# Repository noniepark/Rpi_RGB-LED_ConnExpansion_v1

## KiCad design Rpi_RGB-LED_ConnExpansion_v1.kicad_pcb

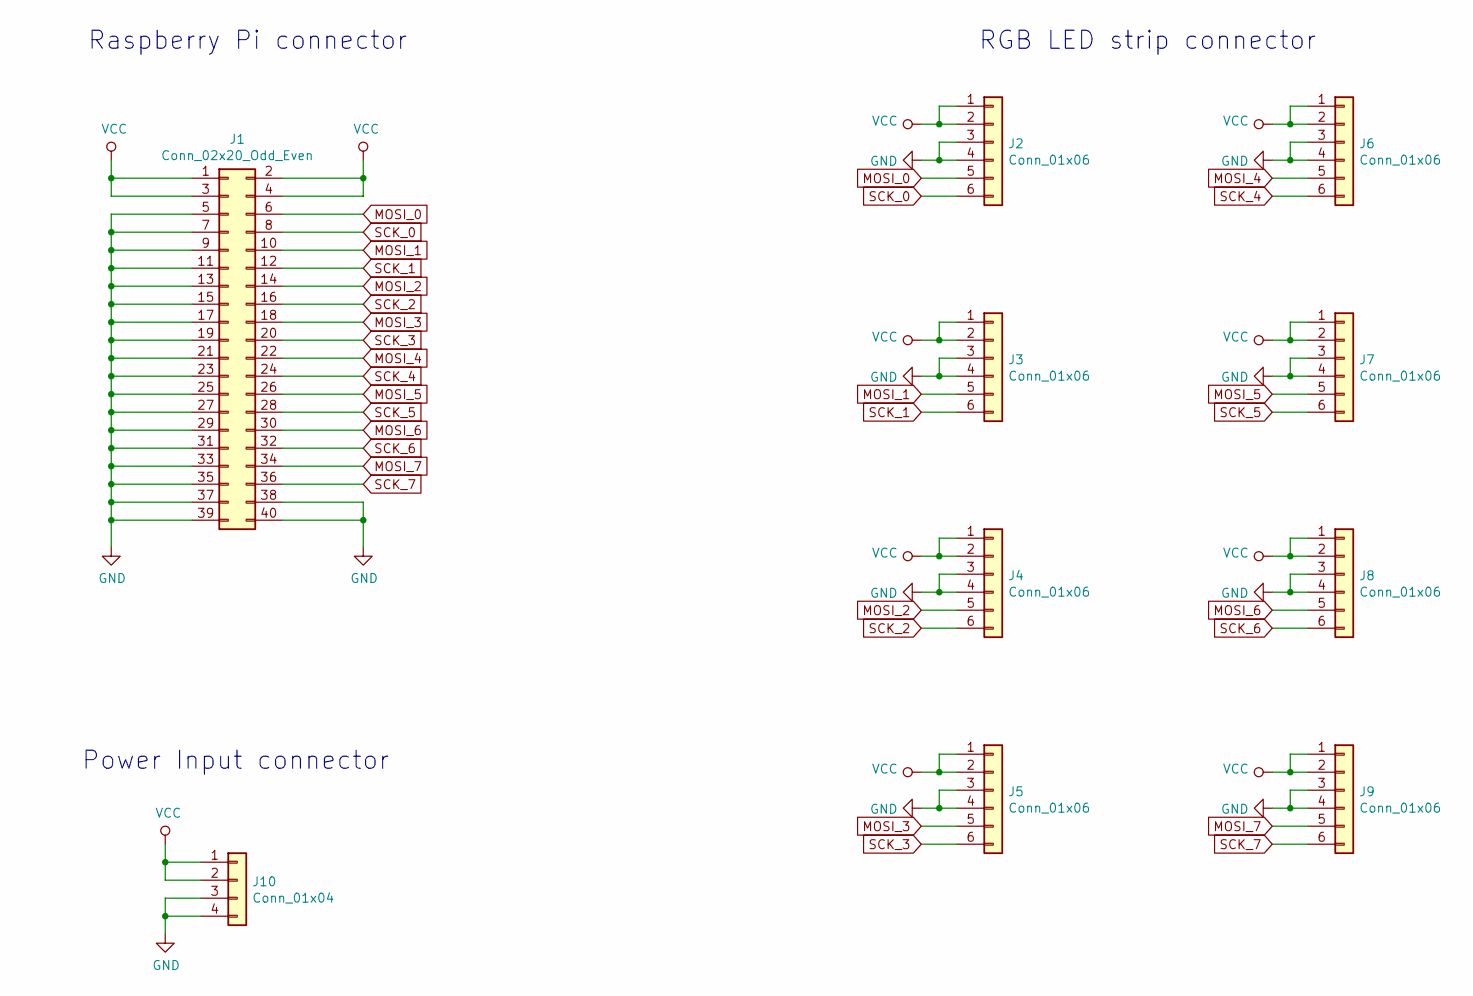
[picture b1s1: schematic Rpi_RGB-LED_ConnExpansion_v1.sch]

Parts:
J1: Conn_02x20_Odd_Even; IDC-Header_2x20_P2.54mm_Vertical
J2, J3, J4, J5, J6, J7, J8, J9: Conn_01x06; DINKLE_5EHDVC-6P
J10: Conn_01x04; DINKLE_DT-55-B01W-04

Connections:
GND: J1.5, J1.7, J1.9, J1.11, J1.13, J1.15, J1.17, J1.19, J1.21, J1.23, J1.25, J1.27, J1.29, J1.31, J1.33, J1.35, J1.37, J1.38, J1.39, J1.40, J2.3, J2.4, J3.3, J3.4, J4.3, J4.4, J5.3, J5.4, J6.3, J6.4, J7.3, J7.4, J8.3, J8.4, J9.3, J9.4, J10.3, J10.4
MOSI_0: J1.6, J2.5
MOSI_1: J1.10, J3.5
MOSI_2: J1.14, J4.5
MOSI_3: J1.18, J5.5
MOSI_4: J1.22, J6.5
MOSI_5: J1.26, J7.5
MOSI_6: J1.30, J8.5
MOSI_7: J1.34, J9.5
SCK_0: J1.8, J2.6
SCK_1: J1.12, J3.6
SCK_2: J1.16, J4.6
SCK_3: J1.20, J5.6
SCK_4: J1.24, J6.6
SCK_5: J1.28, J7.6
SCK_6: J1.32, J8.6
SCK_7: J1.36, J9.6
VCC: J1.1, J1.2, J1.3, J1.4, J2.1, J2.2, J3.1, J3.2, J4.1, J4.2, J5.1, J5.2, J6.1, J6.2, J7.1, J7.2, J8.1, J8.2, J9.1, J9.2, J10.1, J10.2

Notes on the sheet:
RGB LED strip connector
Raspberry Pi connector
Power Input connector

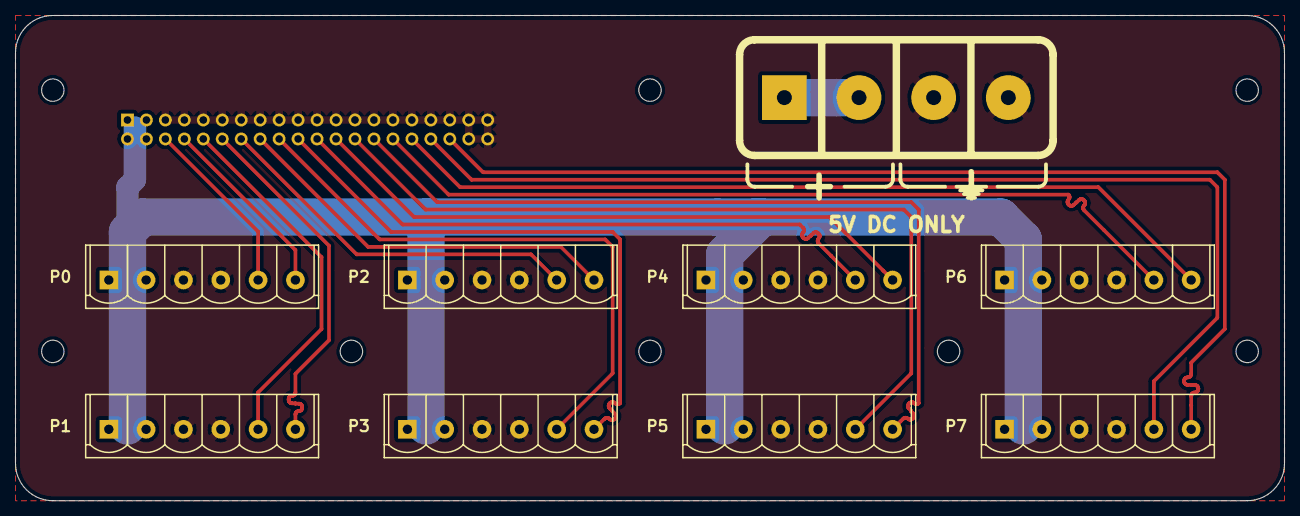
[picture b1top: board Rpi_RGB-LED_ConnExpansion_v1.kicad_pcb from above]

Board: 2 copper layers, 170.0 x 65.0 mm, 10 parts (1 on the bottom side), 18 nets.

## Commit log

2019-04-29 The first commit
